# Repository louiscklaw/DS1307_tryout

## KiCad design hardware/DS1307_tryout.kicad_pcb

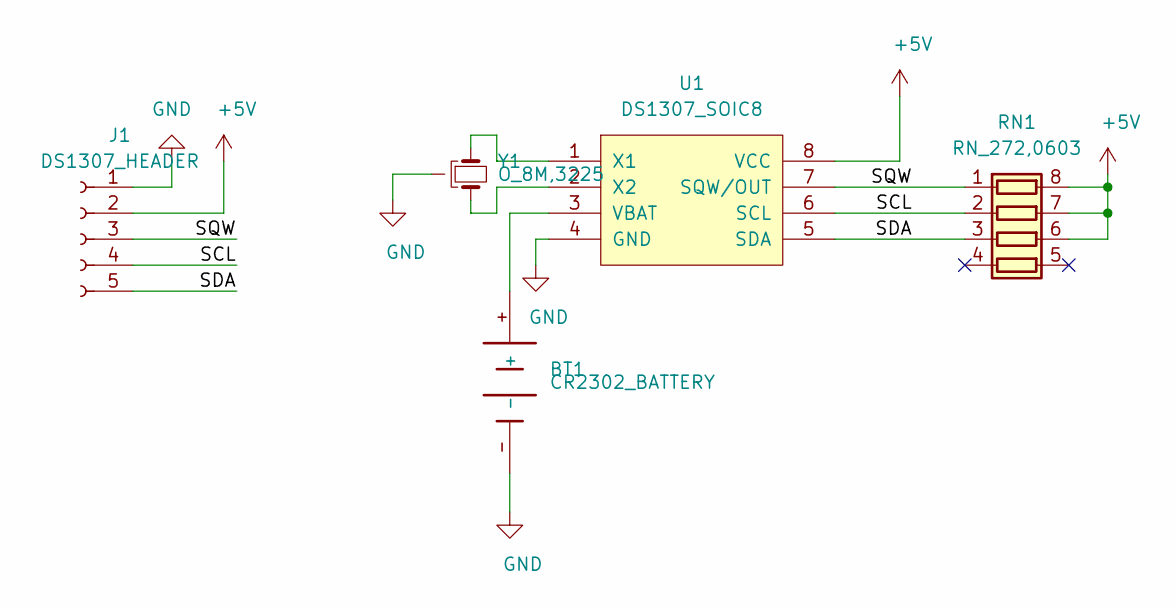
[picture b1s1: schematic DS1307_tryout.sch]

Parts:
BT1: CR2302_BATTERY
J1: DS1307_HEADER; PinHeader_1x05_P1.27mm_Vertical
RN1: RN_272,0603; R_Array_Concave_4x0603
U1: DS1307_SOIC8
Y1: O_8M,3225; OSC_3225

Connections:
+5V: J1.2, RN1.6 (R3.2), RN1.7 (R2.2), RN1.8 (R1.2), U1.8 (VCC)
/SCL: J1.4, RN1.2 (R2.1), U1.6 (SCL)
/SDA: J1.5, RN1.3 (R3.1), U1.5 (SDA)
/SQW: J1.3, RN1.1 (R1.1), U1.7 (SQW/OUT)
GND: BT1.-, J1.1, U1.4 (GND), Y1.2
unnamed: BT1.+, U1.3 (VBAT)
unnamed: U1.1 (X1), Y1.1
unnamed: U1.2 (X2), Y1.3

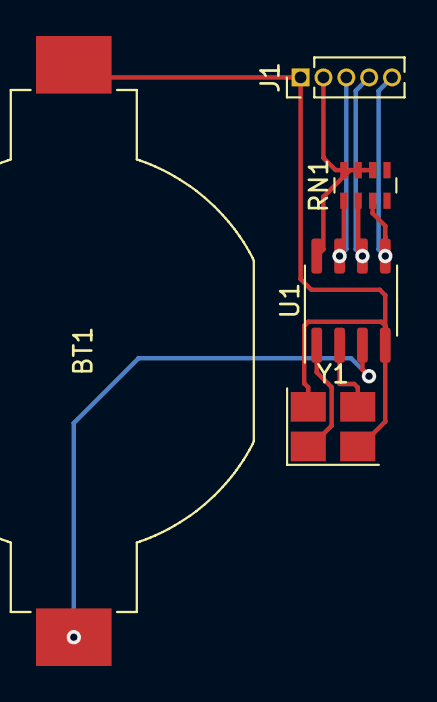
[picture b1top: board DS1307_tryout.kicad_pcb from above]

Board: 2 copper layers, 5 parts (0 on the bottom side), 8 nets.

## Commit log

2019-06-26 update,
2020-05-05 ci: init travis build config,
2020-05-05 ci: init travis token,
